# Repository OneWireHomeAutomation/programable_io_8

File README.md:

# programable_io_8
board with 8 programmable input/output channels

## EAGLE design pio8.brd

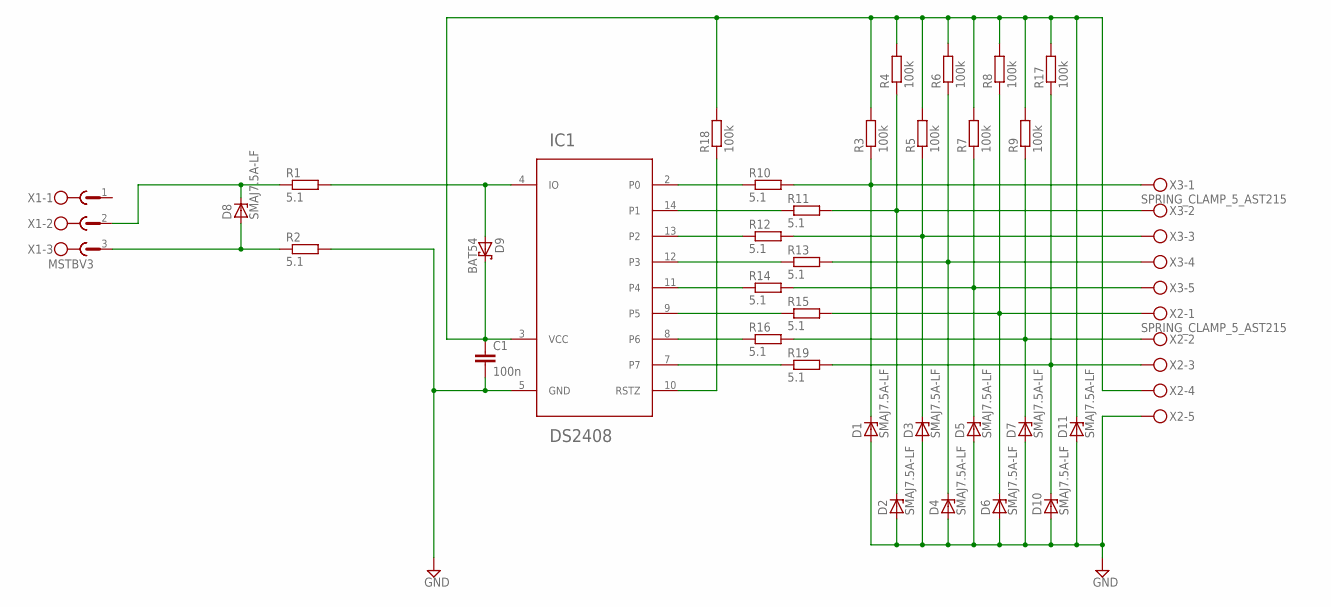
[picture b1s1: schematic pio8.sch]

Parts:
C1: 100n; C0402K
D1, D2, D3, D4, D5, D6, D7, D8, D10, D11: SMAJ7.5A-LF; DO214AC
D9: BAT54; SOT23
IC1: DS2408; SO16
R1, R2, R10, R11, R12, R13, R14, R15, R16, R19: 5.1; R0402
R3, R4, R5, R6, R7, R8, R9, R17, R18: 100k; R0402
X1: MSTBV3
X2, X3: SPRING_CLAMP_5_AST215; AST215_5

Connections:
GND: C1.2, D1.A, D2.A, D3.A, D4.A, D5.A, D6.A, D7.A, D10.A, D11.A, IC1.5 (GND), R2.2, X2.5A, X2.5B
unnamed: D1.C, R3.1, R10.2, X3.1A, X3.1B
unnamed: D2.C, R4.1, R11.2, X3.2A, X3.2B
unnamed: D3.C, R5.1, R12.2, X3.3A, X3.3B
unnamed: D4.C, R6.1, R13.2, X3.4A, X3.4B
unnamed: D5.C, R7.1, R14.2, X3.5A, X3.5B
unnamed: D6.C, R8.1, R15.2, X2.1A, X2.1B
unnamed: D7.C, R9.1, R16.2, X2.2A, X2.2B
unnamed: IC1.2 (P0), R10.1
unnamed 9: D8.A, R2.1, X1.3; also elsewhere on the board
unnamed 10: D8.C, R1.1, X1.2; also elsewhere on the board
unnamed: C1.1, D9.3 (C), D11.C, IC1.3 (VCC), R3.2, R4.2, R5.2, R6.2, R7.2, R8.2, R9.2, R17.2, R18.2, X2.4A, X2.4B
unnamed: D10.C, R17.1, R19.2, X2.3A, X2.3B
unnamed: IC1.14 (P1), R11.1
unnamed: IC1.13 (P2), R12.1
unnamed: IC1.12 (P3), R13.1
unnamed: IC1.11 (P4), R14.1
unnamed: IC1.9 (P5), R15.1
unnamed: IC1.8 (P6), R16.1
unnamed: IC1.7, R19.1
unnamed: D9.1 (A), IC1.4 (IO), R1.2
unnamed: IC1.10 (RSTZ), R18.1

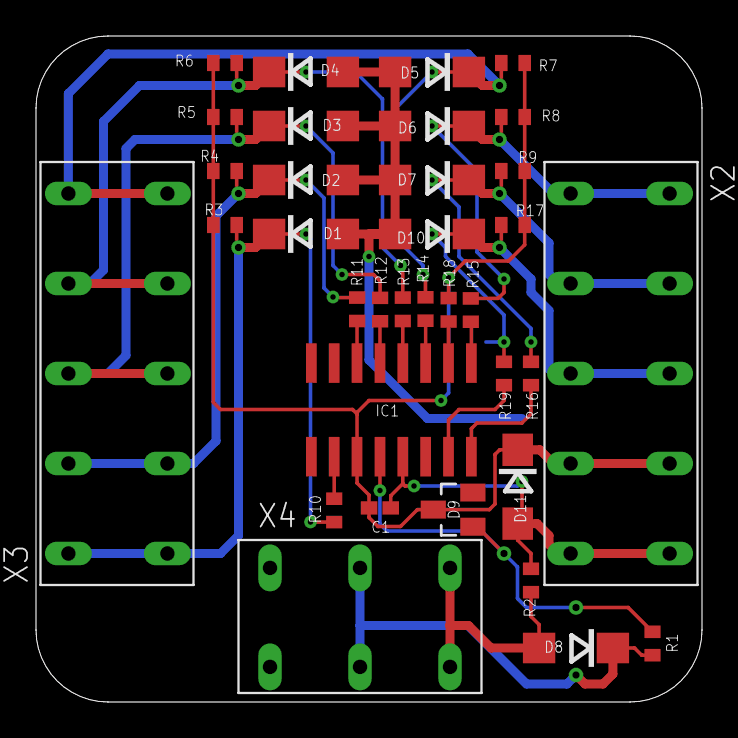
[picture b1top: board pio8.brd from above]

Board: 2 copper layers, 37.0 x 37.0 mm, 35 parts (0 on the bottom side), 22 nets.

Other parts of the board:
X4: SPRING_CLAMP_3_AST215; AST215_3

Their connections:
unnamed 9: X4.3A, X4.3B; also elsewhere on the board
unnamed 10: X4.2A, X4.2B; also elsewhere on the board

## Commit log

2016-06-07 adding first release of the pio8 board
2016-06-10 changing some values: 5 Ohm resistor to 5.1 Ohm (5 Ohm is not broadly available) selected different type of TVS diode with essentially the same ratings
2016-06-10 adding semi automatic release system
2016-06-10 removing absolute paths
2016-06-10 adding cairocffi to install section of .travis.yml to get eagle-bom.py working
2016-06-10 changing travis config to use python
2016-06-18 rotating connectors to resolve issue #1 while maintaining IO and GND/VCC pinout but rotating pinout for the one wire connector (to keep the pin numbering the same as other 1-wire devices have)
2016-06-18 changing the connector solution for the digital i/o's - now using spring clamp terminals instead of pluggable screw terminals. The new ones should reduce the width. Also turning back the 3 pin connec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
2017-01-17 changing 1-wire connector to a spring clamp type
